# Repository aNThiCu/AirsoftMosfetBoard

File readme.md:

This is untested , unstable hardware. The main focus of this version was creating more room for upgrades and manufacturability at home.

The hardware now consists of 2 PCB's one being the control center and the other the necessary sensors. This makes the board be less prone to shorts or mechanical stress from the gearbox of the replica.
The control board will sit inside the buffer tube while the sensor board will stay in the same position.

Being able to make the PCB's at home saves a whole lot of time so the following changes have been made:

    -thick traces of 0.5 width and up , resulting in the need of a less precise CNC
    -most of the traces are only on the front side , thanks to splitting the components across 2 boards
    -components added/modified for protection and well functioning of the boards
    -switched from 5V LDO to 3.3V buck , microcontroller shouldn't reset anymore while using low discharge rate battery

 What's coming next (hopefully):

    -configurable mode selector switch with multiple modes
    -app for ease of use (mby)
    -troubleshooting indicators
    -folder with everything needed for direct manufacturing from a factory
    -different trigger version (optical/magnetic)
    -stress testing results
    -redo of shape for better fitment in V2 gearboxes

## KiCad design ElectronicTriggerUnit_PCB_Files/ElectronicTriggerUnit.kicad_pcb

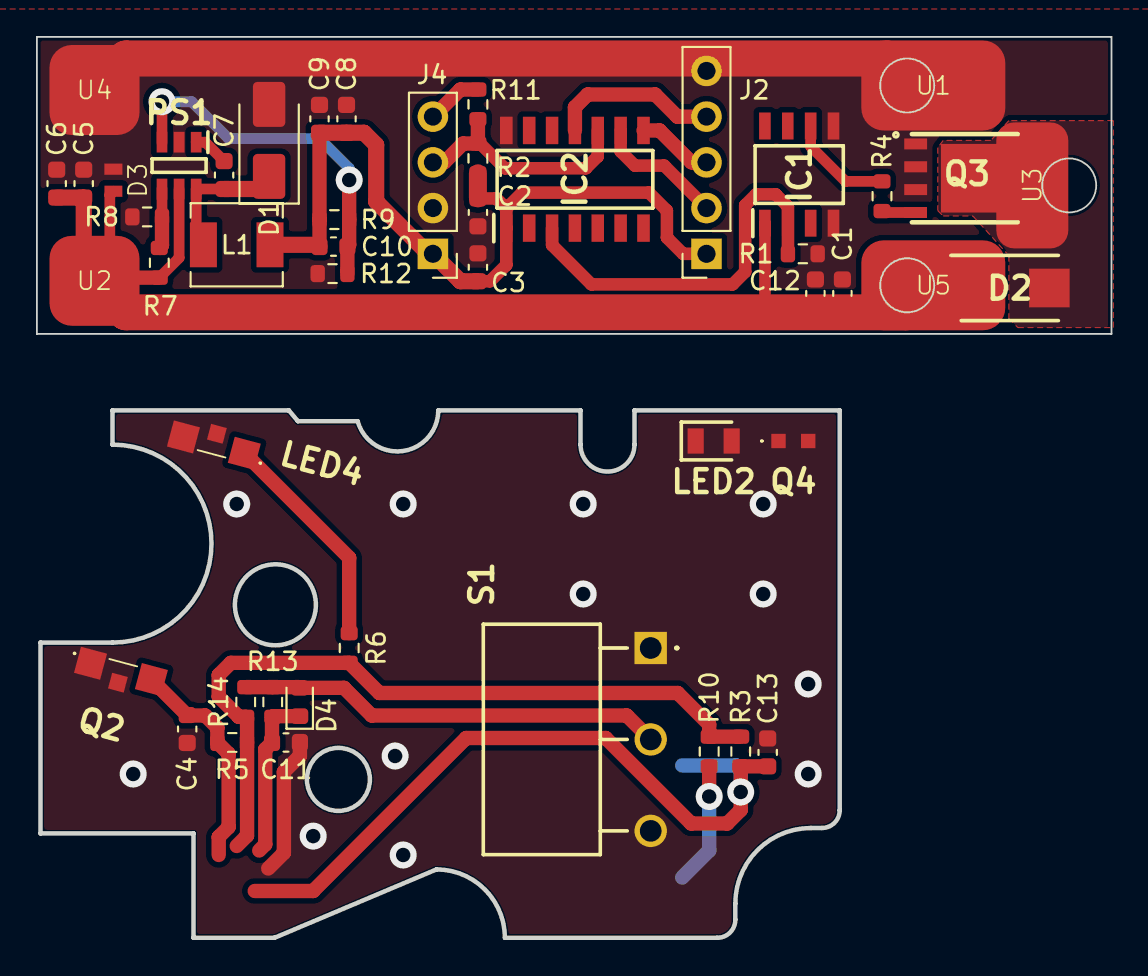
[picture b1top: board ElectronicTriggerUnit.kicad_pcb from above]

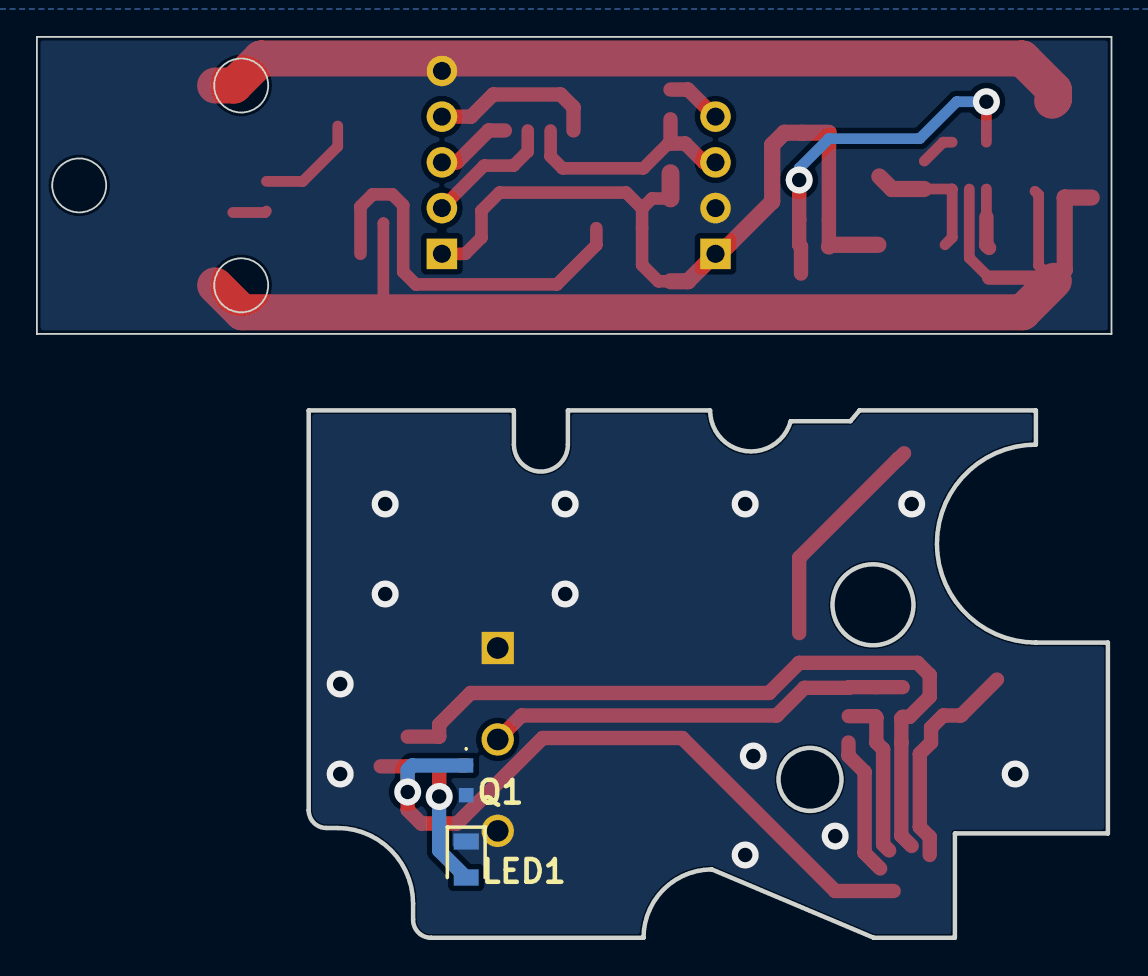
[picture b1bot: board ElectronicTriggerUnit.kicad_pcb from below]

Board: 2 copper layers, 59.5 x 50.0 mm, 50 parts (2 on the bottom side), 22 nets.

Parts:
C1, C2: 1u; C_0603_1608Metric
C3, C4, C13: 10n; C_0603_1608Metric
C5, C6: 10u/1206; C_0603_1608Metric
C7: 22n; C_0603_1608Metric
C8, C9: 22u; C_0603_1608Metric
C10: 100p; C_0603_1608Metric
C11: 100nf; C_0603_1608Metric
C12: 0.1u; C_0603_1608Metric
D1: B340A; D_SMA
D2: SS24; DIOM5436X247N
D3: 824045812; TVS_DIODE
D4: D; D_0603_1608Metric
IC1: MCP1407-E_SN; SOIC127P600X175-8N
IC2: ATTINY814-SSF; SOIC127P600X175-14N
J2: Conn_01x05; PinSocket_1x05_P2.54mm_Vertical
J4: Conn_01x04; PinHeader_1x04_P2.54mm_Vertical
L1: 10u/C2921170; L_Chilisin_BMRA00040420
LED1, LED2: XL-2012IRC-940; LEDC2012X105N
LED4: LKIR30102C-A01; APA3010P3C
PS1: AP5100WG-7; SOT95P285X140-6N
Q1, Q4: LC191PTDT; AP1608P1CP22
Q2: LKPT30102B-A01; APA3010P3C
Q3: 78-SQRS140ELP; POWERPAKSO-8
R1, R2, R3, R5, R7, R9: 10k; R_0603_1608Metric
R4: 10R; R_0603_1608Metric
R6: 51R; R_0603_1608Metric
R8: 2k; R_0603_1608Metric
R10: 91R; R_0603_1608Metric
R11: 1k; R_0603_1608Metric
R12: 3.3k; R_0603_1608Metric
R13: 1K; R_0603_1608Metric
R14: 10K; R_0603_1608Metric
S1: Trigger; 463092691402
U1, U4: Gnd; Copper_Pad
U2, U5: 12v; Copper_Pad
U3: GndMotor; Copper_Pad

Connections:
+3.3V: C2.1, C3.1, C8.1, C9.1, C10.1, IC2.1 (VDD), J2.1, J4.1, L1.2, R2.1, R3.2, R5.2, R6.1, R9.1, R10.1, R14.2
+12V: C1.2, C5.1, C6.1, C12.1, D2.1 (K), D3.1 (K), IC1.1 (VDD_1), PS1.5 (IN), R7.2, U2.1 (Con), U5.1 (Con)
/NMOS: IC1.2 (INPUT), IC2.3 (PA5), R1.2
/Semi_Auto: C13.1, Q1.1 (C), R3.1
/Semi_Auto_In: IC2.8 (PB1), J2.3
/V_Cycle_In: IC2.11 (PA1), J2.4
/V_Cycle_Out: C4.1, Q2.2 (E), R5.1
/V_FB: C10.2, PS1.3 (FB), R9.2, R12.1
/pwr_motor: D2.2 (A), Q3.5, Q3.6, Q3.7, Q3.8, Q3.9, U3.1 (Con)
/trigger_In: IC2.9 (PB0), J2.2
/trigger_Out: C11.2, D4.1 (K), R13.2
/updiRx: IC2.10 (PA0/~RESET/UPDI), J4.3, R2.2, R11.1
/updiTx: J4.4, R11.2
GND: C1.1, C2.2, C3.2, C4.2, C5.2, C6.2, C8.2, C9.2, C11.1, C12.2, C13.2, D1.2 (A), D3.2 (A), IC1.4 (GND_1), IC1.5 (GND_2), IC2.14 (GND), J2.5, J4.2, LED1.1, LED2.1, LED2.2, LED4.2, LED4.3, PS1.2 (GND), Q1.2 (E), Q2.1 (C), Q2.3, Q3.1, Q3.2, Q3.3, Q4.1 (C), Q4.2 (E), R1.1, R8.1, R12.2, S1.1 (COM), S1.3 (NC), U1.1 (Con), U4.1 (Con)
unnamed: C7.2, D1.1 (K), L1.1, PS1.6 (SW)
unnamed: D4.2 (A), R13.1, R14.1, S1.2 (NO)
unnamed: IC1.6 (OUT_1), R4.2
unnamed: LED1.2, R10.2
unnamed: LED4.1, R6.2
unnamed: C7.1, PS1.1 (BST)
unnamed: PS1.4 (EN), R7.1, R8.2
unnamed: Q3.4, R4.1

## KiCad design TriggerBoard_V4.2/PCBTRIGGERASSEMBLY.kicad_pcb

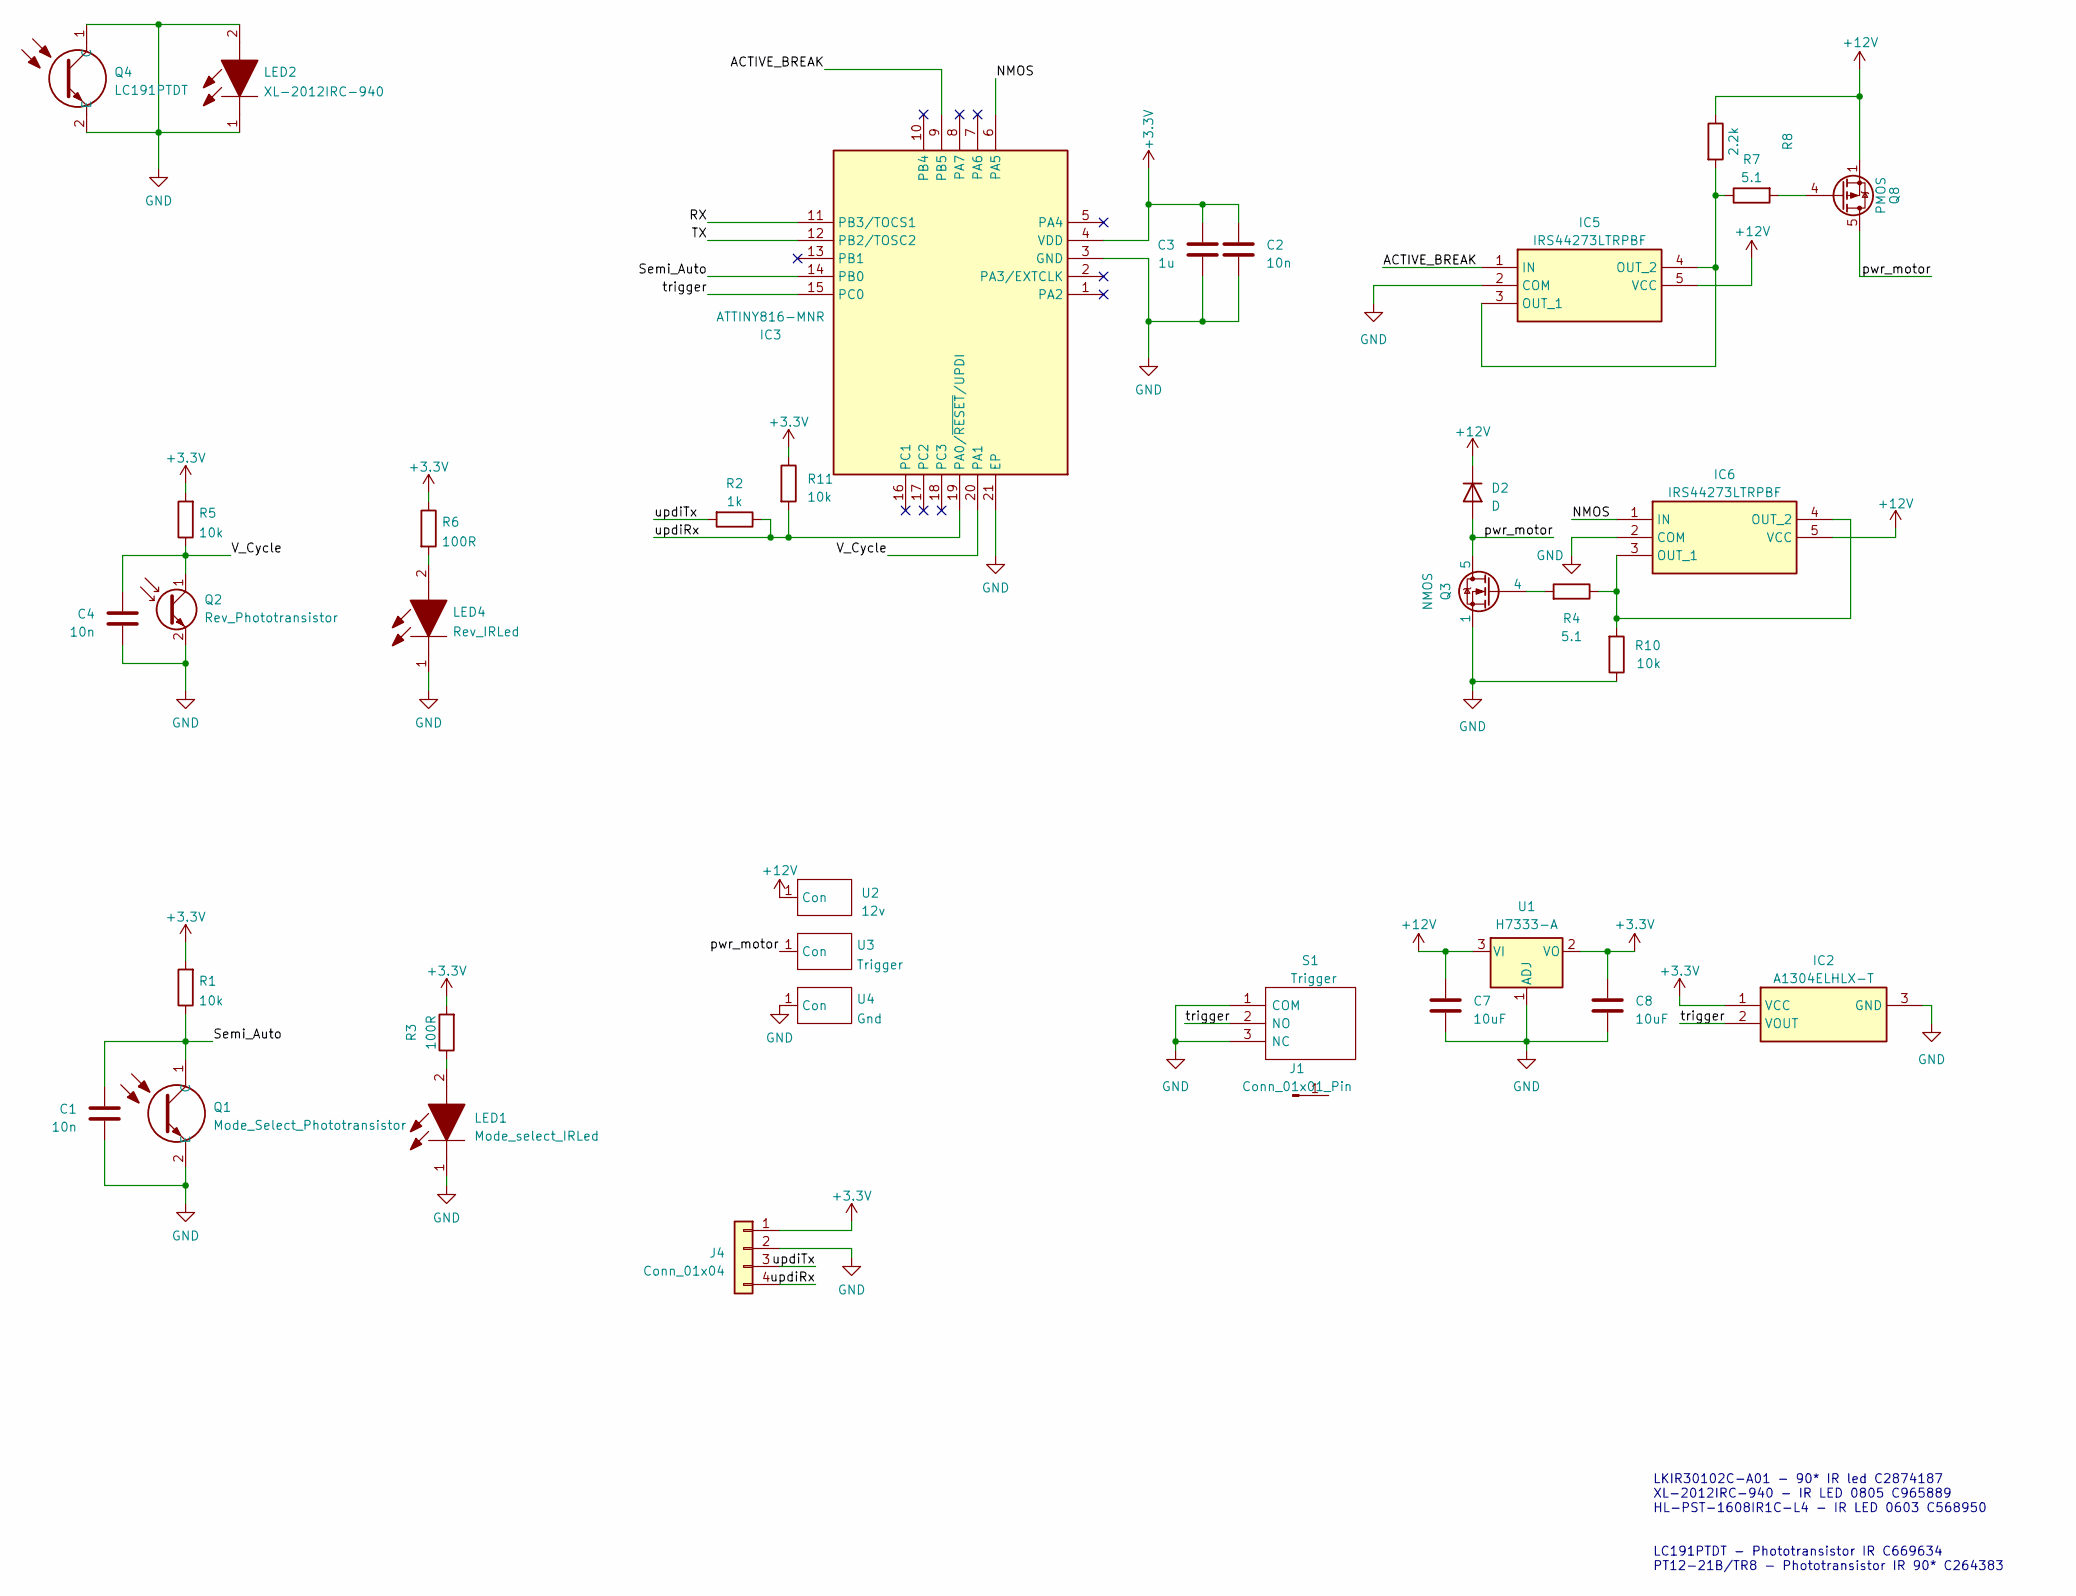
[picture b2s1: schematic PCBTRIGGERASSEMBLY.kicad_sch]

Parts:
C1, C2, C4: 10n; C_0402_1005Metric
C3: 1u; C_0402_1005Metric
C7, C8: 10uF; C_0402_1005Metric
D2: D; SBR3U60P1Q7
IC2: A1304ELHLX-T; SOT95P285X113-3N; Mouser Part Number 250-A1304ELHLX-T
IC3: ATTINY816-MNR; QFN40P300X300X90-21N; Mouser Part Number 579-ATTINY816-MNR
IC5, IC6: IRS44273LTRPBF; SOT95P280X130-5N; Mouser Part Number 942-IRS44273LTRPBF
J1: Conn_01x01_Pin; PinHeader_1x01_P2.54mm_Vertical
J4: Conn_01x04; PinHeader_1x04_P2.54mm_Vertical
LED1: Mode_select_IRLed; LEDC2012X105N; Mouser Part Number 604-APTD2012SF4C
LED2: XL-2012IRC-940; LEDC2012X105N; Mouser Part Number 604-APTD2012SF4C
LED4: Rev_IRLed; APA3010P3C; Mouser Part Number 755-CSL1501RW1
Q1: Mode_Select_Phototransistor; AP1608P1CP22; Mouser Part Number 604-AP1608P1C-P22
Q2: Rev_Phototransistor; APA3010P3C
Q3: NMOS; POWERPAKSO-8
Q4: LC191PTDT; AP1608P1CP22; Mouser Part Number 604-AP1608P1C-P22
Q8: PMOS; POWERPAKSO-8
R1, R5, R10, R11: 10k; R_0402_1005Metric
R2: 1k; R_0402_1005Metric
R3, R6: 100R; R_0402_1005Metric
R4, R7: 5.1; R_0402_1005Metric
R8: 2.2k; R_0402_1005Metric
S1: Trigger; 463092691402; Mouser Part Number 710-463092691402
U1: H7333-A; SOT-89-3
U2: 12v; Copper_pad
U3: Trigger; Copper_pad
U4: Gnd; Copper_pad

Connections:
+3.3V: C2.1, C3.1, C8.2, IC2.1 (VCC), IC3.4 (VDD), J4.1, R1.2, R3.2, R5.2, R6.1, R11.1, U1.2 (VO)
+12V: C7.2, D2.1 (K), IC5.5 (VCC), IC6.5 (VCC), Q8.1 (S), Q8.2 (S), Q8.3 (S), R8.1, U1.3 (VI), U2.1 (Con)
/ACTIVE_BREAK: IC3.9 (PB5), IC5.1 (IN)
/NMOS: IC3.6 (PA5), IC6.1 (IN)
/RX: IC3.11 (PB3/TOCS1)
/Semi_Auto: C1.1, IC3.14 (PB0), Q1.1 (C), R1.1
/TX: IC3.12 (PB2/TOSC2)
/V_Cycle: C4.1, IC3.20 (PA1), Q2.1 (C), R5.1
/pwr_motor: D2.2 (A), Q3.5, Q3.6, Q3.7, Q3.8, Q3.9, Q8.5 (D), Q8.6, Q8.7, Q8.8, Q8.9, U3.1 (Con)
/trigger: IC2.2 (VOUT), IC3.15 (PC0), S1.2 (NO)
/updiRx: IC3.19 (PA0/~RESET/UPDI), J4.4, R2.1, R11.2
/updiTx: J4.3, R2.2
GND: C1.2, C2.2, C3.2, C4.2, C7.1, C8.1, IC2.3 (GND), IC3.3 (GND), IC3.21 (EP), IC5.2 (COM), IC6.2 (COM), J4.2, LED1.1, LED2.1, LED2.2, LED4.1, Q1.2 (E), Q2.2 (E), Q3.1, Q3.2, Q3.3, Q4.1 (C), Q4.2 (E), R10.1, S1.1 (COM), S1.3 (NC), U1.1 (ADJ), U4.1 (Con)
unnamed: IC5.3 (OUT_1), IC5.4 (OUT_2), R7.1, R8.2
unnamed: IC6.3 (OUT_1), IC6.4 (OUT_2), R4.1, R10.2
unnamed: LED1.2, R3.1
unnamed: LED4.2, R6.2
unnamed: Q3.4, R4.2
unnamed: Q8.4 (G), R7.2

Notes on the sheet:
LKIR30102C-A01 - 90* IR led C2874187 XL-2012IRC-940 - IR LED 0805 C965889 HL-PST-1608IR1C-L4 - IR LED 0603 C568950 LC191PTDT - Phototransistor IR C669634 PT12-21B/TR8 - Phototransistor IR 90* C264383

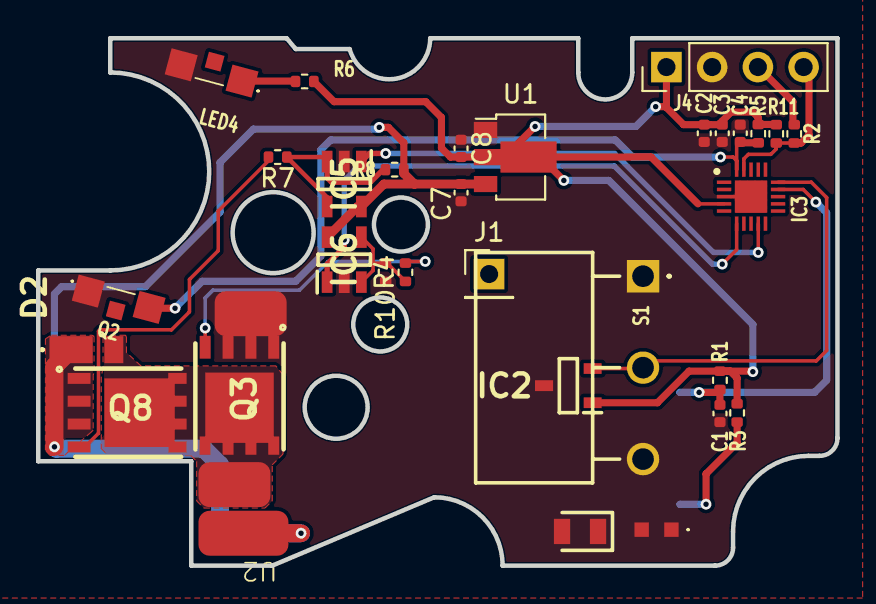
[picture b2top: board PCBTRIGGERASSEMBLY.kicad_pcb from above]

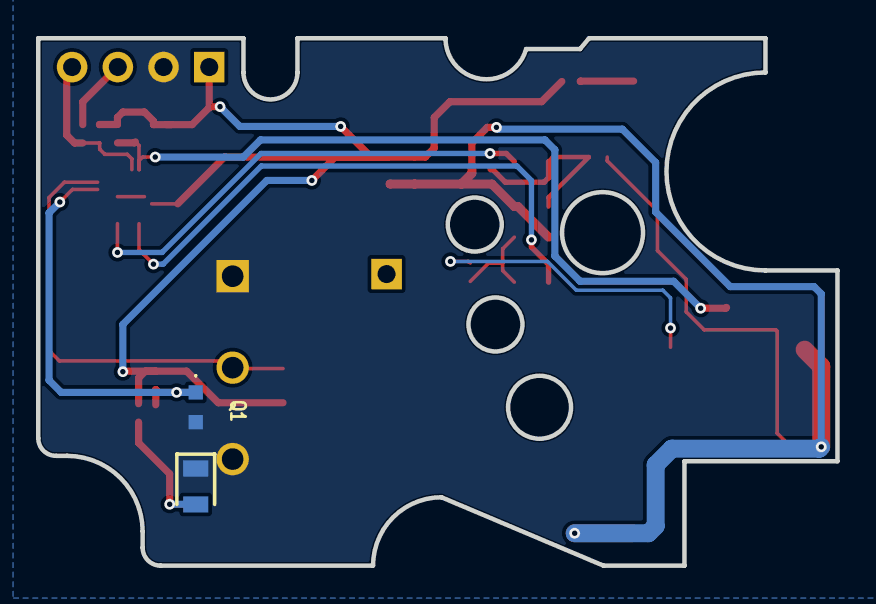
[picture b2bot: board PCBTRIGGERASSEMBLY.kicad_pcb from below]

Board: 2 copper layers, 44.4 x 29.3 mm, 36 parts (2 on the bottom side), 17 nets.

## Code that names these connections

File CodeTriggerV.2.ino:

//pins
  //input
int triggerPin = PIN_PC0;
int cyclePin = PIN_PA1;
int modePin = PIN_PB0;
  //output
int NmosOutput = PIN_PA5;
int BreakOutput = PIN_PB5;
//logic
bool mode = 1;
bool shooting = 0;
bool brk = 0;
//timers
unsigned long int startBreak=0;

void setup() {
  //Input Init
  pinMode(triggerPin, INPUT_PULLUP);
  pinMode(cyclePin, INPUT);
  pinMode(modePin, INPUT);
  //Output Init
  pinMode(NmosOutput, OUTPUT);
  pinMode(BreakOutput, OUTPUT);
  //Output Value Init
  analogWrite(NmosOutput, 0);
  digitalWrite(BreakOutput, 0);
  attachInterrupt(digitalPinToInterrupt(triggerPin), Start_shoot, FALLING);
  attachInterrupt(digitalPinToInterrupt(cyclePin), Cycle_finish, RISING);
}

void Start_shoot() {
  if (shooting == false) {
    brk = 0;
    digitalWrite(BreakOutput, 0);
    analogWrite(NmosOutput, 255);
    shooting = true;
  }
}

void Cycle_finish() {
  if (shooting == true)
  {
    if (mode == 1) {//Semi-auto
      analogWrite(NmosOutput, 0);
      shooting = false;
      brk = 1;
    } else if (digitalRead(triggerPin) == 1) {//Full-auto
      analogWrite(NmosOutput, 0);
      shooting = false;
      brk = 1; 
    }
  }
}

void Start_break()
{
  digitalWrite(BreakOutput, 1);
  startBreak=millis();
}

void Stop_break()
{
  brk=0;
  digitalWrite(BreakOutput,0);
}

void loop() {
  noInterrupts();
  if (brk == 1 && digitalRead(BreakOutput)==0)
    Start_break();
  interrupts();

  if(digitalRead(BreakOutput)==1 && millis()-startBreak>=100)
    Stop_break();

  if (analogRead(modePin) > 55) mode = 0; else mode = 1;  //0=fullauto , 1=semiauto
}

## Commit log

2023-09-03 Add files via upload
    The shooting logic value has been replaced by detaching and attaching interrupts in order to obtain the same results.
2023-09-09 -added modes
    settings can be changed via the ProgrammingModule
2023-09-09 -settings changer
    must be ran before uploading main code, used to change settings
2024-01-30 PCB Files
2025-03-05 complete redo
2025-03-05 redo of project
2025-03-05 modular board version
2025-03-05 added gitignore
2025-03-05 added exceptions
2025-03-05 removed unnecesary files
